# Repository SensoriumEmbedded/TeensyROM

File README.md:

# TeensyROM Multi-capable Cartridge for C64/128

***Connect your Commodore to the 21st century***

**Features include:**
* **TeensyROM+ (PCB v0.4)** is the latest TeensyROM revision — **[see this document](docs/TR+NewFeatures.md)** for additional details:
  * **[TR Host Extensions](docs/TR_Host_Extensions.md)** — Allows others to write and experiment with TR firmware as a .TRH extension, installed alongside the core firmware without modifying it. Envisioned and implemented by [Kelly Fox](https://github.com/kfox) — a huge thank you!
    * [Mean Hamster Power Engine (MPE)](https://meanhamster.com/games/mpe-power-engine) is the first TRH extension, letting your C64 play games never released for it: NES, Game Boy, Doom, classic point-and-click adventures and more. Thank you to [John Swiderski](https://github.com/ziggystar12) for the incredible work and inspiration
  * **Kernal Replacement** — load a custom KERNAL ROM image, with no hardware modification.
  * **512KB REU (RAM Expansion Unit)** — a real REU your C64 software can detect and use
    * Now also works alongside the Retro Replay, Super Snapshot V5, and Final Cartridge III 101% freezers
  * **Freezer Cartridge Support** — Action Replay, Retro Replay, Final Cartridge III and Super Snapshot V5 emulated natively. Thank you to [Paul Harker (LessPaul)](https://github.com/LessPaul) for the freezer contributions!
  * **Remote DMA Memory Access** — give an external app Serial or Ethernet read/write access to C64 memory
    * Supported by [c64cast](https://github.com/kfox/c64cast) — streaming video, audio, visualizations and much more
  * **Battery-Backed Real-Time Clock** — a built-in coin-cell holder: TR+ can remember the correct time through power cycles
  * **External Reset Detect** — press an external reset (C64U button, User port, etc) returns you to the TR menu
  * **Programmable Alternate Button** — the "Alt" button is assignable to whatever's most useful
* All TeensyROM versions:
  * **ROM emulator**: The perfect way to play CRT files, such as the highly recommended [OneLoad64](https://www.youtube.com/watch?v=lz0CJbkplj0) collection.
  * **Instant loader**: [Immediately load/run](docs/General_Usage.md) program (PRG) files
  * **MIDI USB Host & Device, custom ASID Player**: Use a [MIDI keyboard, DAW](docs/MIDI_Usage.md), or [ASID source](docs/ASID_Player.md) to play your SID chip.
  * **Internet interface**: Connect to a [Telnet BBS](docs/Ethernet_Usage.md) or use the integrated [web browser](docs/Browser_Usage.md) to surf/search/download
  * **Remote Control** your C64 using 
    * [NFC Launch System](docs/NFC_Loader.md): The feel of old school cartridges combined with [instant loading](https://www.youtube.com/watch?v=iNfQx2gx0hA)
    * [TeensyROM Suite](https://github.com/MetalHexx/TeensyROM-Suite) (cross-platform): [Trom UI](https://github.com/MetalHexx/TeensyROM-Suite/blob/main/docs/trom-ui.md) with its [DJ Mixer](https://github.com/MetalHexx/TeensyROM-Suite/blob/main/docs/dj-mixer.md), [Trom Terminal](https://github.com/MetalHexx/TeensyROM-Suite/blob/main/docs/trom-terminal.md), the [Trom Agent](https://github.com/MetalHexx/TeensyROM-Suite/blob/main/docs/trom-agent.md) AI companion, and [Trom API](https://github.com/MetalHexx/TeensyROM-Suite/blob/main/docs/trom-api.md) for your own tools
  * SID File Player with voice muting and speed control 
  * Bitmap Picture viewer, Text/PETSCII viewer, Custom BASIC Commands, Autolaunch, *and more* 
  * Lots of games, utilities, pics, and music built-in: no external media required to get started!
  * [**Multiple Hardware Interfaces:**](media/TR_Connections.png) SD card, USB Drive, USB Device and host Ports, Ethernet Port

**C64 Ultimate user?**  See [this list](docs/C64_Ultimate_Enhancements.md) of enhancements the TR brings to your C64U 

*Design by Travis S/Sensorium ([e-mail](mailto:travis@sensoriumembedded.com))* 

||| 
|:--:|:--:|

**Fully assembled/tested TeensyROM+ units** are available via my [Lectronz Shop](https://lectronz.com/products/teensyrom), or via [Tindie](https://www.tindie.com/products/travissmith/teensyrom-cartridge-for-c64128/) or [eBay](https://www.ebay.com/usr/travis_sensorium).

Case/enclosures are available for sale with a new unit (see links above), or [download](3D_Print_Case/3D-Printed-Case-ReadMe.md) and print at home.

Please consider joining us in the [TeensyROM Discord Server](https://discord.gg/ubSAb74S5U) to meet other TeensyROM users, ask questions, provide thoughts/input/feedback, etc.

## Table of contents
  * [TeensyROM Feature Details](#teensyrom-feature-details)
  * [Links to detailed documentation](#links-to-detailed-documentation)
  * [Demo Videos](#demo-videos)
  * [Hardware/PCB Design](#hardware-pcb-design)
  * [Compatibility](#compatibility)
  * [Inspiration and Thank-Yous](#inspiration-and-thank-yous)
  * [Pictures/screen captures](#pictures-screen-captures)

## TeensyROM Feature Details
Compatible with C64 and C128 machines/variants, NTSC and PAL supported.

### **Super fast Loading (.PRG/P00) or ROM emulation (.CRT)** directly from:
  * USB thumb Drive
  * SD card
  * Teensy Internal Flash Memory
  * Transfer directly from your computer using [Trom UI](https://github.com/MetalHexx/TeensyROM-Suite/blob/main/docs/trom-ui.md#copy-files-to-your-cart) (drag and drop, or watch folders), [Trom Terminal](https://github.com/MetalHexx/TeensyROM-Suite/blob/main/docs/trom-terminal.md#copy-files) or [Trom Agent](https://github.com/MetalHexx/TeensyROM-Suite/blob/main/docs/trom-agent.md) from the [TeensyROM Suite](https://github.com/MetalHexx/TeensyROM-Suite)
  * See supported file details [here](https://github.com/SensoriumEmbedded/TeensyROM/blob/main/docs/General_Usage.md#loading-files-and-emulating-roms)
  * [NFC Loading system](docs/NFC_Loader.md) available to quickly select/load with NFC tags.
### **MIDI in/out via USB Host connection:** 
  * Play your SID with a USB MIDI keyboard!
  * Use with popular software such as **Cynthcart, Station64** etc, or the included MIDI2SID app
  * Supports all regular MIDI messages **in and out**
    * Can use your C64 to play a MIDI sound capable device.
  * **Sequential, Datel/Siel, Passport/Sentech, and Namesoft** MIDI cartridges emulated 
  * Use a USB Hub for multiple instruments+thumb drive access
### **MIDI in via USB Device connection:** 
  * Stream .SID or .MIDI files from a modern computer directly to your Commodore machine SID chip!
  * Play MIDI files out of your PC into C64 apps such as Cynthcart or the MIDI2SID app
  * Stream .SID files out of your PC using the ASID MIDI protocol to hear any SID file on original hardware.
### **Internet communication via Ethernet connection**
  * Connect to your favorite C64/128 Telnet BBS!
  * Use with released software such as **CCGMS, StrikeTerm2014, DesTerm128,** etc
  * **Swiftlink** cartridge + 38.4k modem emulation
  * Send AT commands from terminal software to configure the Ethernet connection
  * Sets C64 system time from internet
### **Firmware updates directly from SD card or USB thumb drive**
  * Just drop the .hex file on an SD card or USB drive, no need for extra software to update.

**Key parameters** (startup, Ethernet, timezone, etc.) are stored in internal EEPROM and retained after power down.

## Links to detailed documentation
  * **Usage Documents**
    * **[General Usage](docs/General_Usage.md)**
    * **[MIDI Usage](docs/MIDI_Usage.md)**
    * **[ASID Player](docs/ASID_Player.md)**
    * **[Ethernet Usage](docs/Ethernet_Usage.md)**
    * **[NFC Loading System](docs/NFC_Loader.md)**
    * **[TeensyROM Web Browser](docs/Browser_Usage.md)**
    * **[GEOS 64](docs/GEOS64_Usage.md)**
    * **[GEOS 128](docs/GEOS128_Usage.md)**
    * **[Custom BASIC Commands](docs/Custom_BASIC_Commands.md)**
    * **[TR Host Extensions (TR+ only)](docs/TR_Host_Extensions.md)**
    * **[USB/Ethernet Remote Command Protocol](docs/ControlComms.md)**
  * **SW Release notes/development**
    * **[Firmware Release history](bin/TeensyROM/FW_Release_History.md)**
    * **[Software Build Instructions](Source/BuildInfo.md)**
  * **Hardware & PCB Related**
    * **[3D printed case files/document](3D_Print_Case/3D-Printed-Case-ReadMe.md)**
    * **[RTC Battery Addition for v0.2/0.3 PCBs](docs/RTC_Battery_Addition.md)**
    * **[TeensyROM Assembly Instructions](PCB/PCB_Assembly.md)**
    * **[PCB Design History](PCB/PCB_History.md)**
    * **[Bill of materials with cost info](https://github.com/SensoriumEmbedded/TeensyROM/raw/main/PCB/v0.3/TeensyROM%20v0.3%20BOM.xlsx)**
    * **[PDF Schematic](https://github.com/SensoriumEmbedded/TeensyROM/raw/main/PCB/v0.3/TeensyROM_v0.3_Schem.pdf)**

## Demo Videos:
  * **[This YouTube Playlist](https://www.youtube.com/playlist?list=PL3fTdu8e_1iChAsRr9KjWtC3A8Ql8IaDn)** contains all the latest TeensyROM demo videos, such as: 
    * Real-time video/audio capture of menu navigation and loading/running/emulating various programs/cartridges
    * Demo using Cynthcart and Datel MIDI emulation to play with a USB keyboard 
    * MIDI ASID Demo: Stream .SID & .MIDI files directly to your C64/SID
    * Web Browser and internet file download demo 
    * SID Player and Picture viewer demo 
  * **[SID DJ on Commodore 64 (ft. TeensyROM)](https://youtu.be/PjhqYkmsScg)**: SID tunes mixed live on real C64s in the Trom UI [DJ Mixer](https://github.com/MetalHexx/TeensyROM-Suite/blob/main/docs/dj-mixer.md), plus a [Scratch / Beat Juggle](https://youtu.be/xoJBOEPB5IY) preview

## Compatibility
* TeensyROM compatability has been fully validated on **many** different NTSC **and** PAL machines: C64, C64C, SX-64, and C128 as well as modern reproductions such as the C64U, Ultimate 64, EVO64, Mega65 (r5 and higher), and Reloaded MKII
* The early "prototype" version of breadbin (PCA 326298 w/ 5 pin video) has a known issue with the reset circuit that must be corrected to be compatible with the TeensyROM and other fastload cartridges. See [this post](https://www.lemon64.com/forum/viewtopic.php?t=74222) or [this video](https://youtu.be/agDFLPP9yIw?t=813) for instructions on how to correct this issue.
* Some NTSC C128s show an intermittent DMA write issue (used by REU, Remote DMA, etc.) — see **[TR+ NTSC C128 DMA Findings](docs/TR+NTSC_C128_DMA_Findings.md)** for symptoms, cause, and the fix.

## Hardware/PCB Design
PCB 0.2/0.3 Component selection was done using parts large enough (SOIC and 0805s at the smallest) that any soldering enthusiast should be able to assemble themselves.   Since high volume production wasn't necessarily the vision for this device, 2 sided SMT was used to reduce the PCB size while still accommodating larger IC packages.

*The original TR (v0.2/0.3) — publicly self-buildable today; see [assembly instructions](PCB/PCB_Assembly.md).*

Beginning with PCB v0.4 (TeensyROM+) the package sizes are reduced (TSSOP and 0603 passives) to allow additional needed circuitry and single sided manufacturing.

**A note about overclocking**
The Teensy 4.1 is slightly "overclocked" to 816MHz from FW in this design. Per the app, external cooling is not required for this speed.  However, in abundance of caution, a heatsink is specified in the BOM for this project.  In addition, the temperature can be read on the setup screen of the main TeensyROM app. The max spec is 95C, and there is a panic shutdown at 90C.  In my experience, even on a warm day running for hours with no heatsink, the temp doesn't exceed 75C.

## Inspiration and Thank-Yous:
* [**Heather S**](https://www.instagram.com/dalliancecreations/): Loving wife, continuous encourager, saintly patience
* [**MetalHexx**](https://github.com/MetalHexx): Big picture ideas, remote control via the [TeensyROM Suite](https://github.com/MetalHexx/TeensyROM-Suite), testing, friendship
* [**Kelly Fox**](https://github.com/kfox): TR+ contributions ([Host Extensions](docs/TR_Host_Extensions.md), build system and much more), [c64cast](https://github.com/kfox/c64cast)
* [**John Swiderski**](https://github.com/ziggystar12) of Mean Hamster Software: [MPE](https://meanhamster.com/games/mpe-power-engine), the first TR Host Extension, and the inspiration behind them
* [**Paul Harker aka LessPaul**](https://github.com/LessPaul): Freezer cartridge contributions (Action Replay, Retro Replay, Final Cartridge III, Super Snapshot V5)
* [**Avrilcadabra**](https://www.youtube.com/@avrilcadabra): Musician, experimenter, provider of ideas and feedback 
* [**Paul D aka Digitalman**](https://www.youtube.com/@digitalman4404): Thought provoker, promoter, Maker, and tester extraordinaire
* [**Stefan Wessels**](https://github.com/StewBC): Cartridge case design
* [**StatMat**](https://github.com/Stat-Mat): NFC Scanner idea, Fast boot code, OneLoad64 creation
* **Giants with tall shoulders**: SID/SIDEKick, KungFu Flash, VICE Team

## Pictures/screen captures:
|||
|:--:|:--:|

|||
|:--:|:--:|
|||
|||

See the [media](media/) folder for more pics and screen shots.

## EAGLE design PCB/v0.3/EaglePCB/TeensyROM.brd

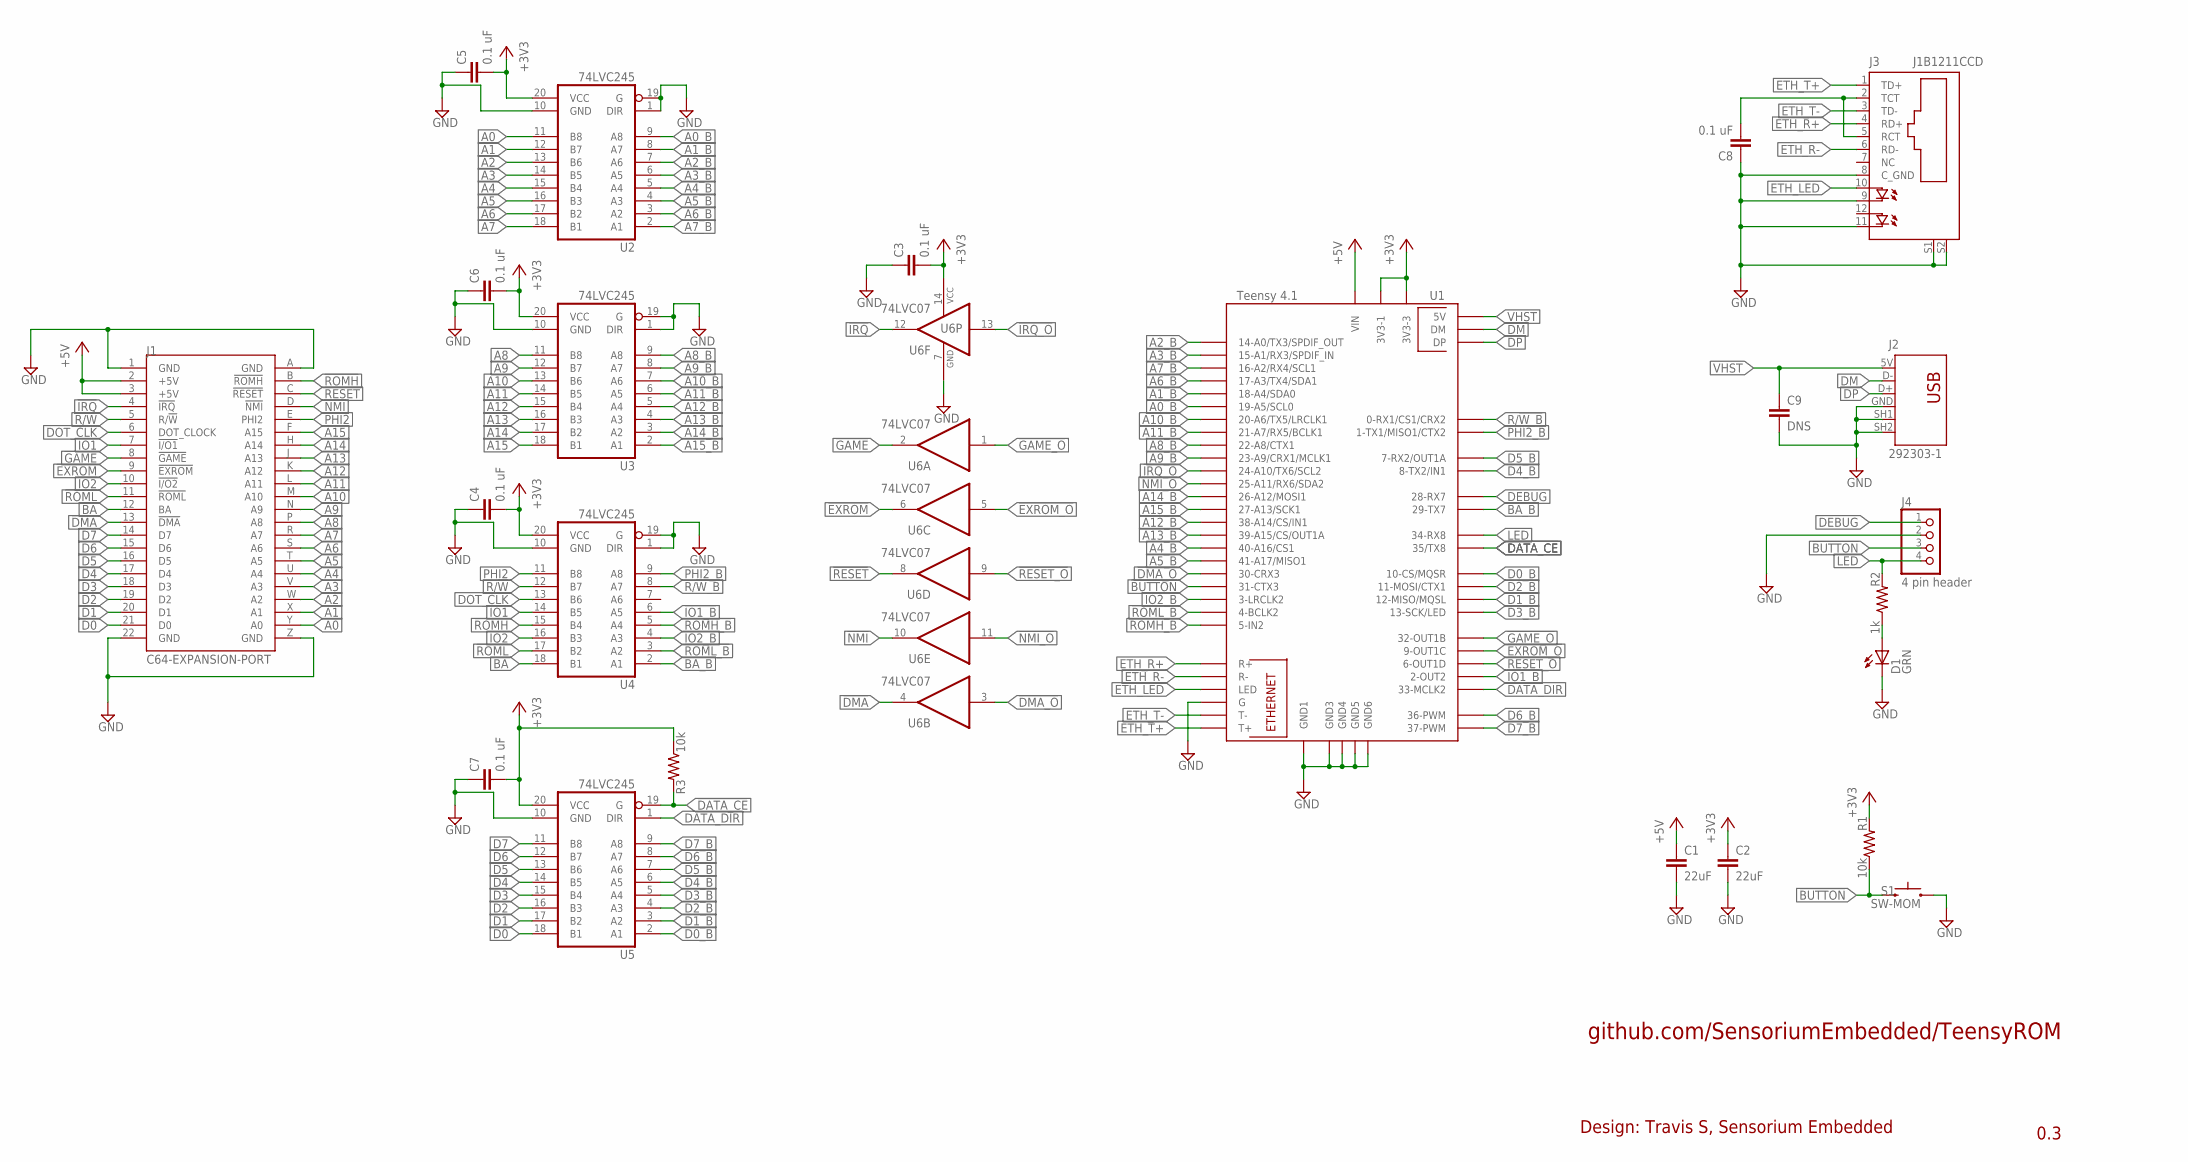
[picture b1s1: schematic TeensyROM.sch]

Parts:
C1, C2: 22uF; C1210
C3, C4, C5, C6, C7, C8: 0.1 uF; 0805
C9: DNS; C1210
D1: GRN; LED-3MM-PTH
J1: C64-EXPANSION-PORT; EXPANSIO_SQ
J2: 292303-1; USB
J3: J1B1211CCD; CONN12_J1B1211CCD_WIZ
J4: 4 pin header; 1X04
R1, R3: 10k; R0805
R2: 1k; R0805
S1: SW-MOM; TACTILE-PTH
U1: Teensy 4.1; TEENSY41
U2, U3, U4, U5: 74LVC245; SO20W
U6: 74LVC07; SO14

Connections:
!BUTTON: J4.3, R1.1, S1.3 (2), U1.31-CTX3
!DATA_CE: R3.2, U1.35-TX8 (35/TX8), U5.19 (G)
!DMA: J1.13 (!DMA), U6.4 (O)
!DMA_O: U1.30-CRX3, U6.3 (I)
!EXROM: J1.9 (!EXROM), U6.6 (O)
!EXROM_O: U1.9-OUT1C, U6.5 (I)
!GAME: J1.8 (!GAME), U6.2 (O)
!GAME_O: U1.32-OUT1B, U6.1 (I)
!IO1: J1.7 (!I/O1), U4.14 (B5)
!IO1_B: U1.2-OUT2, U4.6 (A5)
!IO2: J1.10 (!I/O2), U4.16 (B3)
!IO2_B: U1.3-LRCLK2, U4.4 (A3)
!IRQ: J1.4 (!IRQ), U6.12 (O)
!IRQ_O: U1.24-A10/TX6/SCL2, U6.13 (I)
!NMI: J1.D (!NMI), U6.10 (O)
!NMI_O: U1.25-A11/RX6/SDA2, U6.11 (I)
!RESET: J1.C (!RESET), U6.8 (O)
!RESET_O: U1.6-OUT1D, U6.9 (I)
!ROMH: J1.B (!ROMH), U4.15 (B4)
!ROMH_B: U1.5-IN2, U4.5 (A4)
!ROML: J1.11 (!ROML), U4.17 (B2)
!ROML_B: U1.4-BCLK2, U4.3 (A2)
+3V3: C2.1, C3.2, C4.2, C5.2, C6.2, C7.2, R1.2, R3.1, U1.3V3-1, U1.3V3-3, U2.20 (VCC), U3.20 (VCC), U4.20 (VCC), U5.20 (VCC), U6.14 (VCC)
+5V: C1.1, J1.2 (+5V), J1.3 (+5V), U1.VIN
A0: J1.Y (A0), U2.11 (B8)
A0_B: U1.19-A5/SCL0, U2.9 (A8)
A1: J1.X (A1), U2.12 (B7)
A1_B: U1.18-A4/SDA0, U2.8 (A7)
A2: J1.W (A2), U2.13 (B6)
A2_B: U1.14-A0/TX3/SPDIF_OUT, U2.7 (A6)
A3: J1.V (A3), U2.14 (B5)
A3_B: U1.15-A1/RX3/SPDIF_IN, U2.6 (A5)
A4: J1.U (A4), U2.15 (B4)
A4_B: U1.40-A16/CS1, U2.5 (A4)
A5: J1.T (A5), U2.16 (B3)
A5_B: U1.41-A17/MISO1, U2.4 (A3)
A6: J1.S (A6), U2.17 (B2)
A6_B: U1.17-A3/TX4/SDA1, U2.3 (A2)
A7: J1.R (A7), U2.18 (B1)
A7_B: U1.16-A2/RX4/SCL1, U2.2 (A1)
A8: J1.P (A8), U3.11 (B8)
A8_B: U1.22-A8/CTX1, U3.9 (A8)
A9: J1.N (A9), U3.12 (B7)
A9_B: U1.23-A9/CRX1/MCLK1, U3.8 (A7)
A10: J1.M (A10), U3.13 (B6)
A10_B: U1.20-A6/TX5/LRCLK1, U3.7 (A6)
A11: J1.L (A11), U3.14 (B5)
A11_B: U1.21-A7/RX5/BCLK1, U3.6 (A5)
A12: J1.K (A12), U3.15 (B4)
A12_B: U1.38-A14/CS/IN1, U3.5 (A4)
A13: J1.J (A13), U3.16 (B3)
A13_B: U1.39-A15/CS/OUT1A, U3.4 (A3)
A14: J1.H (A14), U3.17 (B2)
A14_B: U1.26-A12/MOSI1, U3.3 (A2)
A15: J1.F (A15), U3.18 (B1)
A15_B: U1.27-A13/SCK1, U3.2 (A1)
BA: J1.12 (BA), U4.18 (B1)
BA_B: U1.29-TX7, U4.2 (A1)
D0: J1.21 (D0), U5.18 (B1)
D0_B: U1.10-CS\MQSR (10-CS/MQSR), U5.2 (A1)
D1: J1.20 (D1), U5.17 (B2)
D1_B: U1.12-MISO/MQSL, U5.3 (A2)
D2: J1.19 (D2), U5.16 (B3)
D2_B: U1.11-MOSI/CTX1, U5.4 (A3)
D3: J1.18 (D3), U5.15 (B4)
D3_B: U1.13-SCK/LED, U5.5 (A4)
D4: J1.17 (D4), U5.14 (B5)
D4_B: U1.8-TX2/IN1, U5.6 (A5)
D5: J1.16 (D5), U5.13 (B6)
D5_B: U1.7-RX2/OUT1A, U5.7 (A6)
D6: J1.15 (D6), U5.12 (B7)
D6_B: U1.36-PWM, U5.8 (A7)
D7: J1.14 (D7), U5.11 (B8)
D7_B: U1.37-PWM, U5.9 (A8)
DATA_DIR: U1.33-MCLK2, U5.1 (DIR)
DEBUG: J4.1, U1.28-RX7
DM: J2.D- (2), U1.DM
DOT_CLK: J1.6 (DOT_CLOCK), U4.13 (B6)
DP: J2.D+ (3), U1.DP
ETH_CT: C8.2, J3.2 (TCT), J3.5 (RCT)
ETH_LED: J3.10 (A), U1.LED
ETH_R+: J3.4 (RD+), U1.R+
ETH_R-: J3.6 (RD-), U1.R-
ETH_T+: J3.1 (TD+), U1.T+
ETH_T-: J3.3 (TD-), U1.T-
GND: C1.2, C2.2, C3.1, C4.1, C5.1, C6.1, C7.1, C8.1, C9.2, D1.K (C), J1.1 (GND), J1.22 (GND), J1.A (GND), J1.Z (GND), J2.GND (4), J2.SH1 (5), J2.SH2 (6), J3.8 (C_GND), J3.9 (C), J3.11 (C1), J3.S1, J3.S2, J4.2, S1.1, U1.G, U1.GND1, U1.GND3, U1.GND4, U1.GND5, U1.GND6, U2.1 (DIR), U2.10 (GND), U2.19 (G), U3.1 (DIR), U3.10 (GND), U3.19 (G), U4.1 (DIR), U4.10 (GND), U4.19 (G), U5.10 (GND), U6.7 (GND)
LED: J4.4, R2.2, U1.34-RX8
LED_R: D1.A, R2.1
PHI2: J1.E (PHI2), U4.11 (B8)
PHI2_B: U1.1-TX1/MISO1/CTX2, U4.9 (A8)
R/!W: J1.5 (R/!W), U4.12 (B7)
R/!W_B: U1.0-RX1/CS1/CRX2, U4.8 (A7)
VHST: C9.1, J2.5V (1), U1.+5V (5V)

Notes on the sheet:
0.3
github.com/SensoriumEmbedded/TeensyROM
Design: Travis S, Sensorium Embedded

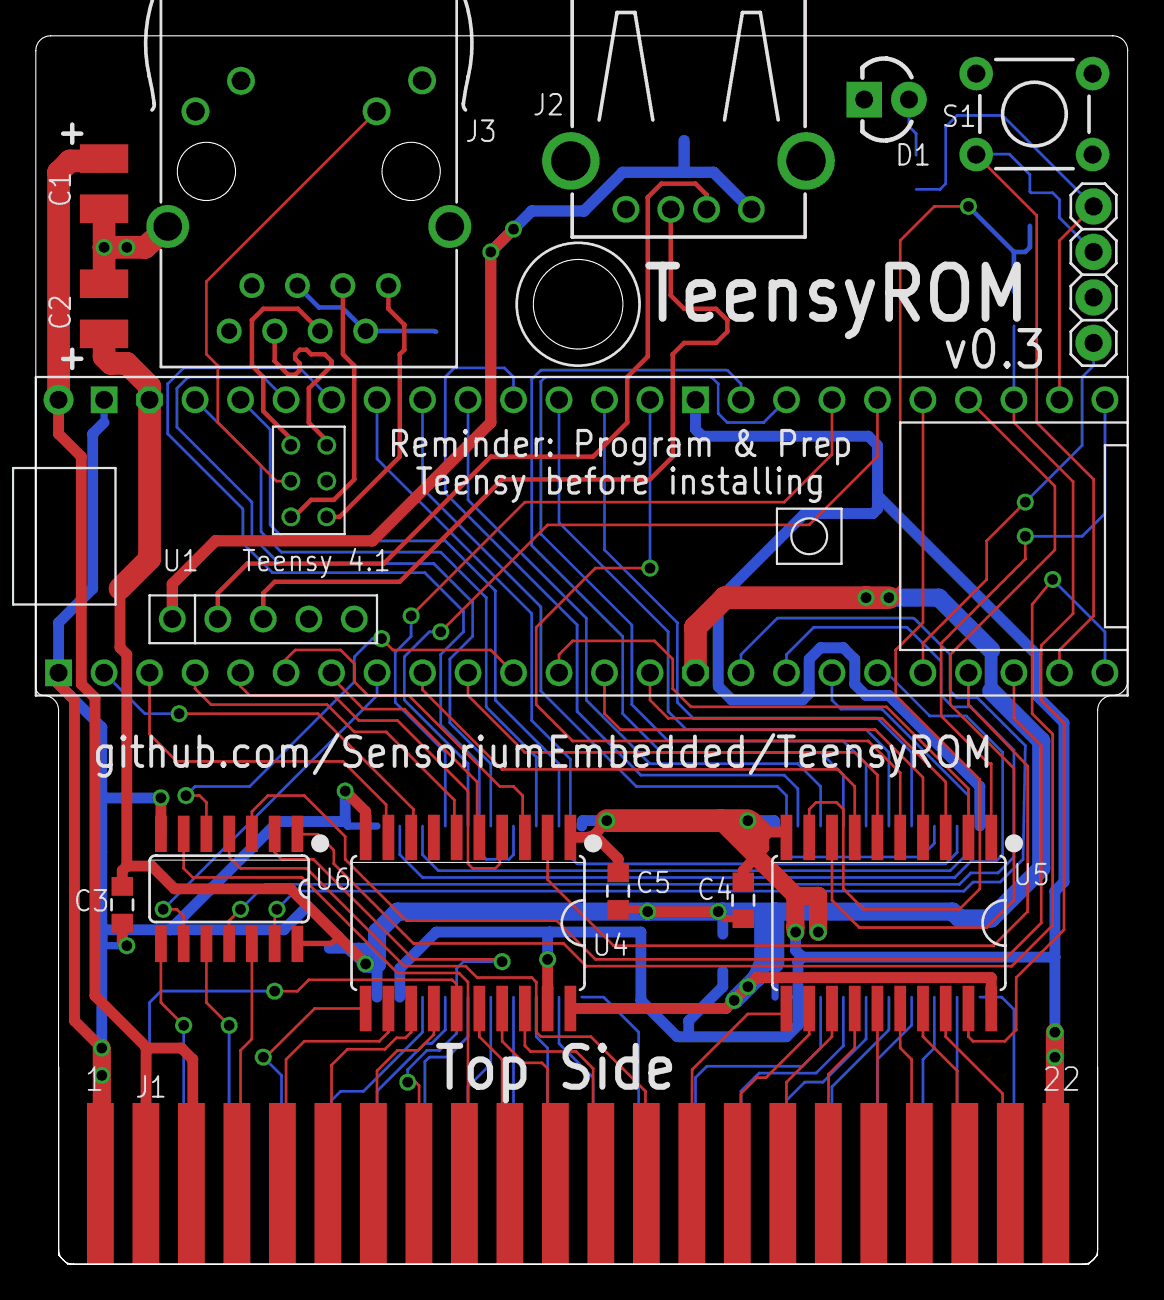
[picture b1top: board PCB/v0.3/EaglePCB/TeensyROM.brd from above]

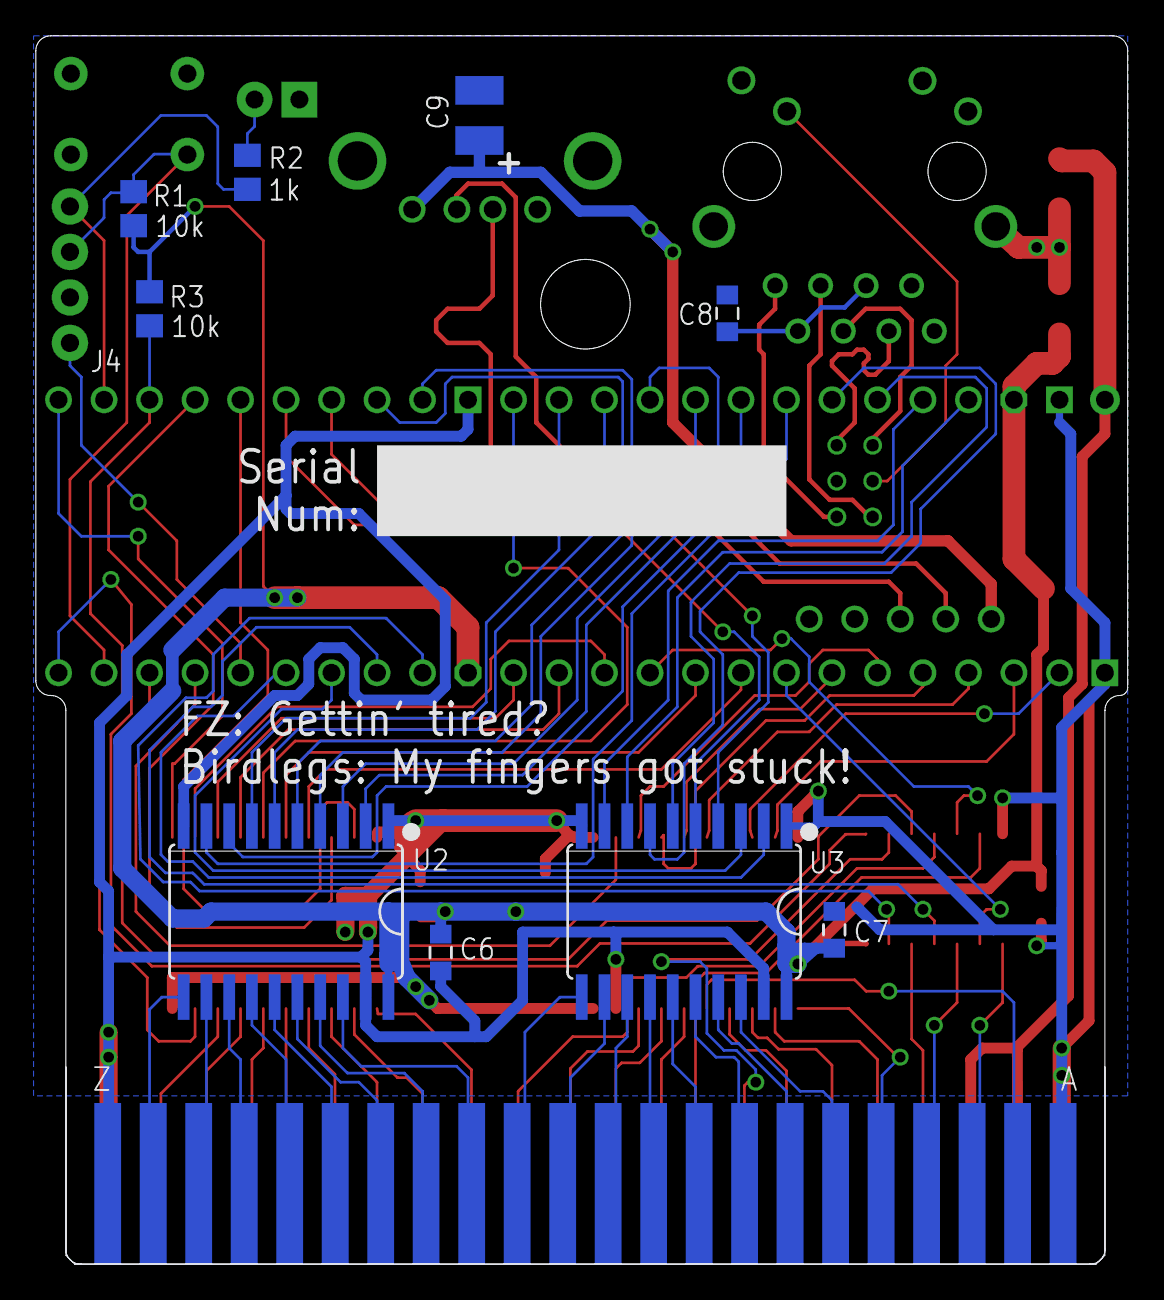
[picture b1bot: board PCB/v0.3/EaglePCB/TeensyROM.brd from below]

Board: 2 copper layers, 61.0 x 68.6 mm, 25 parts (9 on the bottom side), 93 nets.

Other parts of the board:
U$1: 3,0

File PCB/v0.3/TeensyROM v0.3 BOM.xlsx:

BOM item # | Qty | Locations/RefDes | Value | Manuf | MPN Highlighted=No Sub | DigiKey PN/link | Cost ea (USD) July 2023 | Extended Cost (USD) | Notes
1 | 1 | PCB | 2 layer 0.063" PCB | OSH Park, JLCPCB, PCBWay | TeensyROM v0.2c | n/a | 10.799999999999999 | 10.799999999999999 | 2 layer board: 2.40 x 2.70 x 0.063 inches Recommend ENIG finish, 30° chamfered 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
2 | 1 | R2 | RES 0805 1K | TE Connectivity | CRG0805F1K0 | A106056CT-ND | 0.1 | 0.1
3 | 2 | R1,R3 | RES 0805 10K | TE Connectivity | CRG0805F10K | A106054CT-ND | 0.1 | 0.2
4 | 6 | C3, C4, C5, C6, C7,C8 | CAP 0805 CER 0.1UF 50V X7R | Samsung | CL21B104KBCNNNC | 1276-1003-1-ND | 0.1 | 0.60000000000000009
5 | 4 | U2, U3, U4, U5 | 74LVC245, SO20W/N | Nexperia Texas Instruments Texas Instruments | 74LVC245AD,118 (Wide) SN74LVC245ADW (Wide) SN74LVC245ANSR (Nar) | 1727-3104-1-ND 296-1232-5-ND 296-13632-1-ND | 0.68 | 2.72 | Octal Bus Transceiver, 3-state Recommend wide package, but any of these 3 will 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
6 | 1 | U6 | 74LVC07, SO14 | Texas Instruments OnSemi | SN74LVC07ADR MC74LCX07 | 296-8441-1-ND MC74LCX07DR2GOSCT-ND | 0.5 | 0.5 | Hex BUFFER, open collector HV output Either of these two will work
7 | 1 | U1 | Teensy 4.1 Devel Board w/ Ethernet | PJRC | TEENSY41 | 1568-DEV-16771-ND | 33.08 | 33.08 | Be sure to pre-program and then cut the 5v power jumper on the back (see assy i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
8 | 2 | U1-Hdr 1/2 | CONN HEADER VERT 1x24 POS 2.54mm (0.1") | Würth | 61302411121 | 732-5331-ND | 1.31 | 2.62 | For Teensy main connections to TeensyROM
9 | 1 | U1-Hdr 3 | CONN HEADER VERT 1x5 POS 2.54mm (0.1") | Würth | 61300511121 | 732-5318-ND | 0.26 | 0.26 | For Teensy USB Host connection to TeensyROM.
10 | 1 | U1-Hdr 4 | CONN HEADER VERT 6POS (2x3) 2MM | METZ CONNECT | PR20C03VBDN | 1849-1000-ND | 0.19 | 0.19 | For Teensy Ethernet connection to TeensyROM.
11 | 1 | S1 | SW-MOM-TACTILE | C&K | PTS645SL50-2 LFS | CKN9092-ND | 0.19 | 0.19
12 | 1 | D1 | LED-3MM-GRN | Lumex Opto | SSL-LX3044GD | 67-1060-ND | 0.43 | 0.43 | Polarity: Sq hole = short lead = flat side = '-'(Neg) = Cathode
13 | 2 | C1, C2 | CAP CER 22UF 16V X5R 1210 | Samsung | CL32A226MOJNNNE | 1276-1851-1-ND | 0.37 | 0.74
14 | 1 | J3 | RJ-45 w/ Transformer | Cetus/WIZNet | J1B1211CCD | 1278-1052-ND | 3.78 | 3.78 | CONN JACK 1PORT 100 BASE-T PCB
15 | 1 | J2 | USB-A Female | TE/AMP | 292303-1 | A31726-ND | 1.61 | 1.61 | CONN RCPT USB2.0 TYPEA 4POS R/A
16 | 1 | U1 Heatsink | 12x12mm Aluminum heatsink w/ thermal tape attached Max height to fit in case: ~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 | Jeteokar | B0B7K2TWZM | https://www.amazon.com/dp/B0B7K2TWZM or https://www.ebay.com/itm/115401351474 | 0.499 | 0.499 | Optional, but recommended Can sub other 12x12mm heatsinks/pads
16a | 1 | U1 Therm Pad | 11x11mm Thermal Conductive Adhesive Tape | Multiple subs, such as these w/ thermal tape attached | t-Global TG-T1000-11-11-0.25-5PT | 1168-TG-T1000-11-11-0.25-5PT-ND | 0.2 | 0.2 | If needed (recommended heatsink has thermal pad included)
17 | 1 | C9 | 1210 cap | Do not stuff |  |  |  |  | Not required
18 | 1 | J4 | CONN HEADER VERT 1x4 POS 0.1" | Do not stuff |  |  |  |  | Not required
19 | 1 | J1 | C64-EXPANSION-PORT Gold Fingers | Do not stuff |  |  |  |  | Part of PCB
20 | 2 | U1-Rcpt 1/2 | CONN RCPT VERT 1x24 POS 0.1" |  |  |  |  |  | if socketting Teensy
21 | 1 | U1-Rcpt 3 | CONN RCPT VERT 1x5 POS 0.1" |  |  |  |  |  | if socketting Teensy USB
22 | 1 | U1-Rcpt 4 | CONN RCPT 6POS 0.079 PCB | METZ CONNECT | FR20C03VBDN | 1849-1152-ND |  |  | if socketting Teensy Eth
23 | 1 | U1-EthDongl | Ethernet Kit for Teensy 4.1 | PJRC | ETHERNET_KIT |  |  |  | if not using on-board conns
24 | 1 | U1-USBDongl | USB Host Cable For Teensy 4.1 | PJRC | CABLE_USB_HOST_T36 |  |  |  | if not using on-board conns
 |  |  |  |  |  |  | Raw Total: | 58.518999999999998
 |  |  |  |  |  |  | 10% S&H | 5.8519000000000005
 |  |  |  |  |  |  | Parts total | 64.370900000000006
 |  |  |  |  |  |  | Hand Assy+test | 15 | 1 hour labor
 |  |  |  |  |  | Total: Assembled and tested |  | 79.370900000000006
 |  |  |  |  |  |  | Plus shipping | tbd

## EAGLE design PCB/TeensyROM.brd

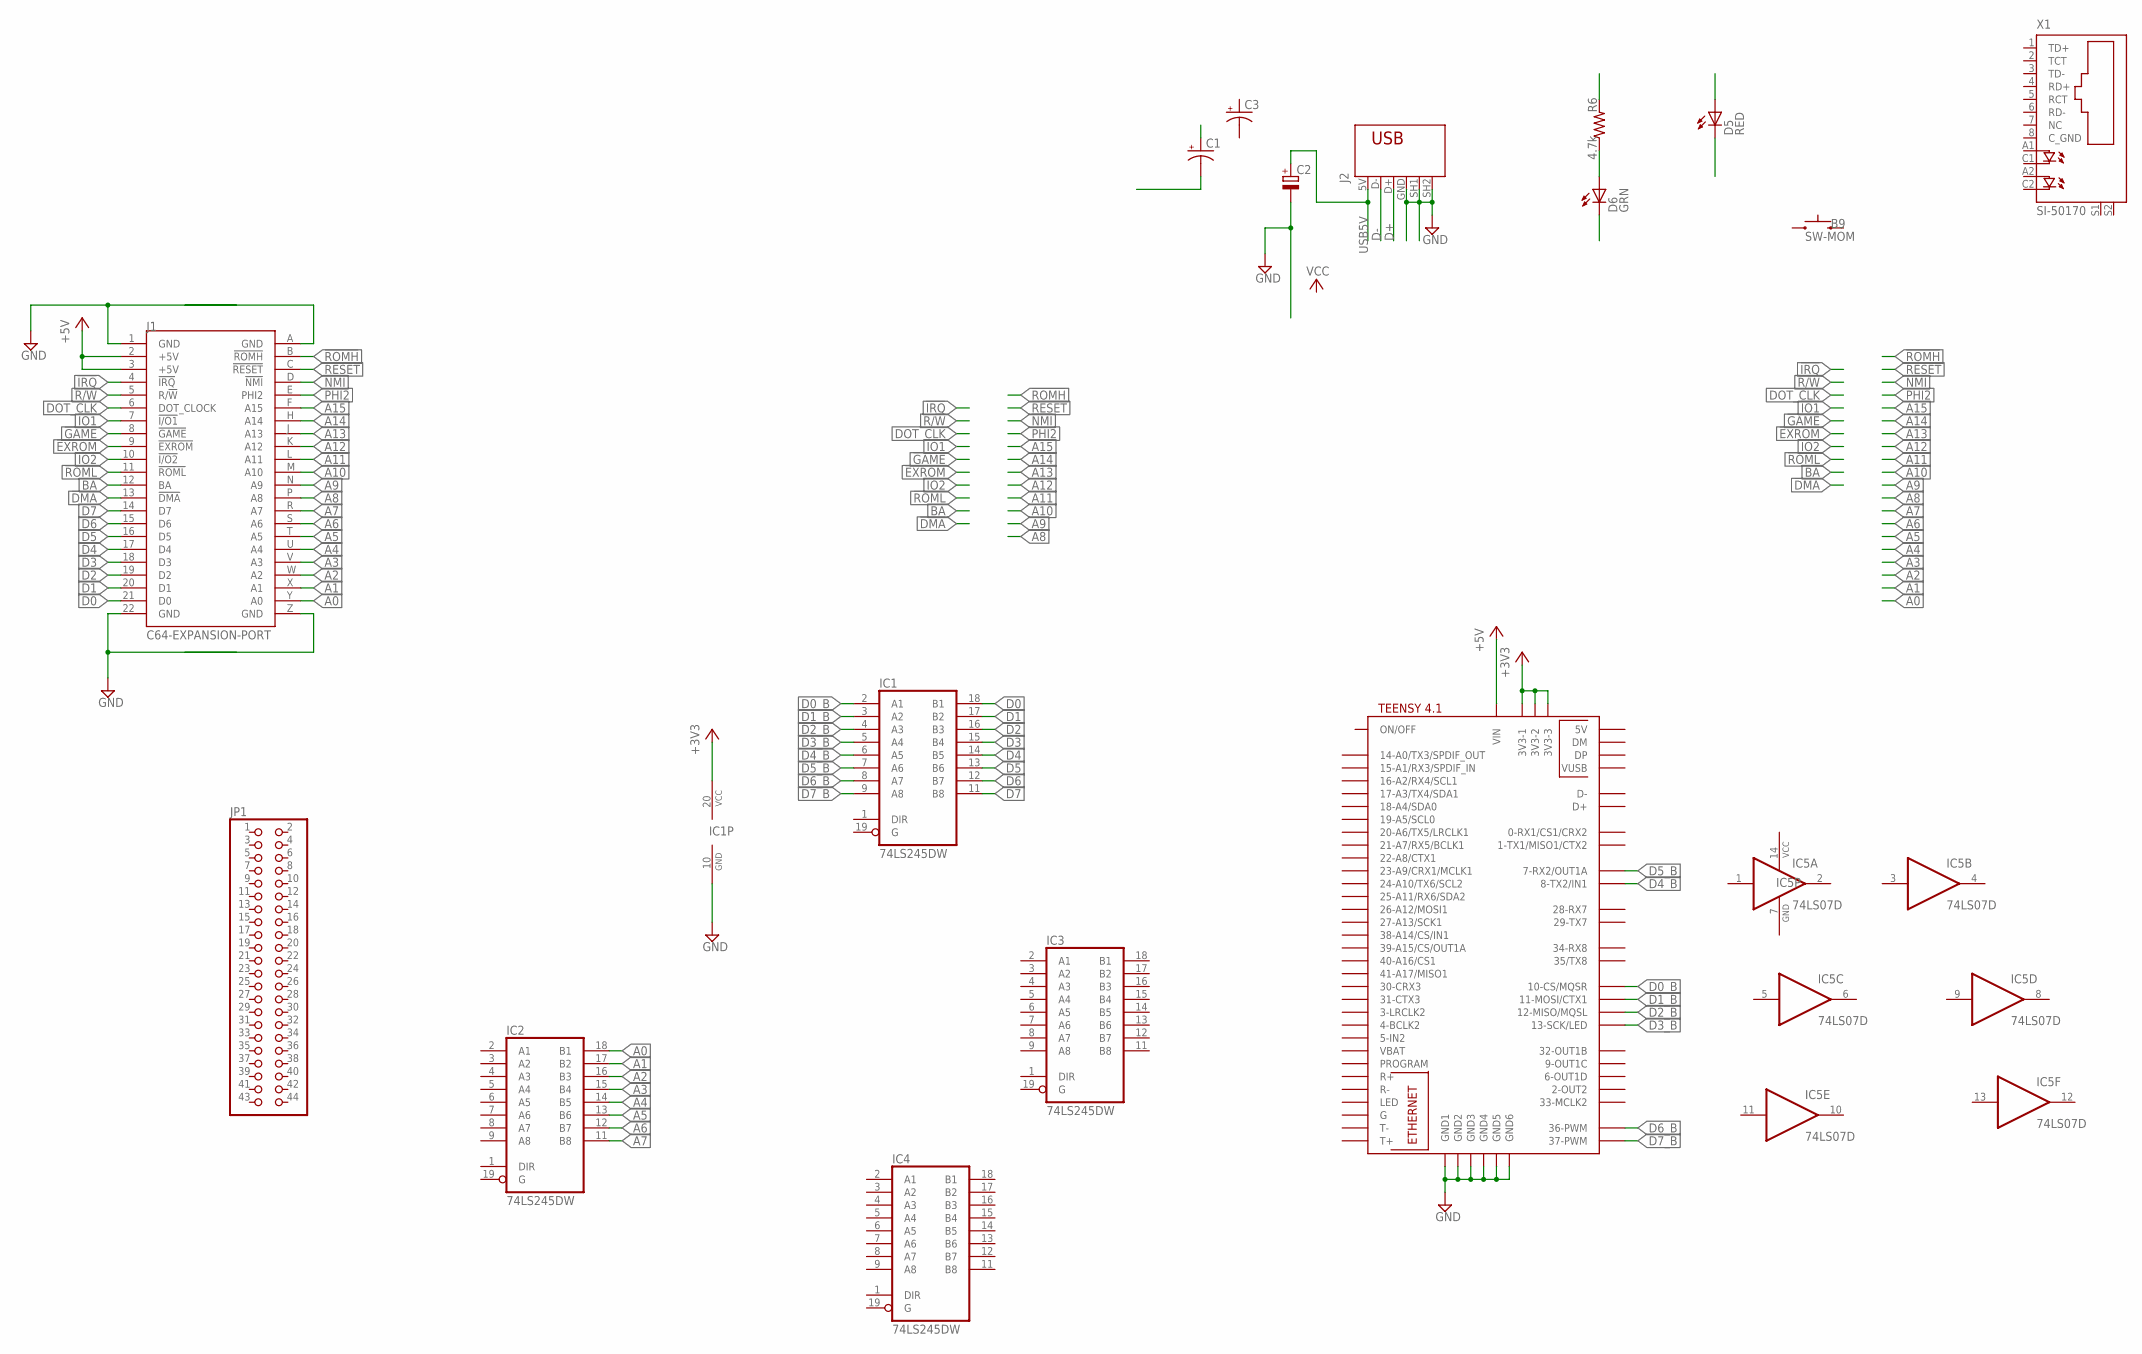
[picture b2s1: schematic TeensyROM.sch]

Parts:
B9: SW-MOM; TACTILE-PTH
C1, C3: CPOL-USE2.5-6; E2,5-6
C2: CPOL-EUA/3216-18W; A/3216-18W
D5: RED; LED-3MM-PTH
D6: GRN; LED-3MM-PTH
IC1, IC2, IC3, IC4: 74LS245DW; SO20W
IC5: 74LS07D; SO14
J1: C64-EXPANSION-PORT; EXPANSIO_SQ
J2: USB-787616; USB
JP1: PINHD-2X22; 2X22
R6: 4.7k; R0805
U$1: TEENSY41
X1: SI-50170

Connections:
!DMA: J1.13 (!DMA)
!EXROM: J1.9 (!EXROM)
!GAME: J1.8 (!GAME)
!IO1: J1.7 (!I/O1)
!IO2: J1.10 (!I/O2)
!IRQ: J1.4 (!IRQ)
!NMI: J1.D (!NMI)
!RESET: J1.C (!RESET)
!ROMH: J1.B (!ROMH)
!ROML: J1.11 (!ROML)
+3V3: IC1.20 (VCC), U$1.3V3-1, U$1.3V3-2, U$1.3V3-3
+5V: J1.2 (+5V), J1.3 (+5V)
+5V1: C1.+
A0: IC2.18 (B1), J1.Y (A0)
A1: IC2.17 (B2), J1.X (A1)
A2: IC2.16 (B3), J1.W (A2)
A3: IC2.15 (B4), J1.V (A3)
A4: IC2.14 (B5), J1.U (A4)
A5: IC2.13 (B6), J1.T (A5)
A6: IC2.12 (B7), J1.S (A6)
A7: IC2.11 (B8), J1.R (A7)
A8: J1.P (A8)
A9: J1.N (A9)
A10: J1.M (A10)
A11: J1.L (A11)
A12: J1.K (A12)
A13: J1.J (A13)
A14: J1.H (A14)
A15: J1.F (A15)
B12: D5.K (C)
BA: J1.12 (BA)
D0: IC1.18 (B1), J1.21 (D0)
D0_B: IC1.2 (A1), U$1.10-CS\MQSR (10-CS/MQSR)
D1: IC1.17 (B2), J1.20 (D1)
D1_B: IC1.3 (A2), U$1.11-MOSI/CTX1
D2: IC1.16 (B3), J1.19 (D2)
D2_B: IC1.4 (A3), U$1.12-MISO/MQSL
D3: IC1.15 (B4), J1.18 (D3)
D3_B: IC1.5 (A4), U$1.13-SCK/LED
D4: IC1.14 (B5), J1.17 (D4)
D4_B: IC1.6 (A5), U$1.8-TX2/IN1
D5: IC1.13 (B6), J1.16 (D5)
D5_B: IC1.7 (A6), U$1.7-RX2/OUT1A
D6: IC1.12 (B7), J1.15 (D6)
D6_B: IC1.8 (A7), U$1.36-PWM
D7: IC1.11 (B8), J1.14 (D7)
D7_B: IC1.9 (A8), U$1.37-PWM
D+: J2.D+ (3)
D-: J2.D- (2)
DOT_CLK: J1.6 (DOT_CLOCK)
GND: C2.-, IC1.10 (GND), IC2.10 (GND), IC3.10 (GND), IC4.10 (GND), IC5.7 (GND), J1.1 (GND), J1.22 (GND), J2.GND (4), J2.SH1 (5), J2.SH2 (6), U$1.GND1, U$1.GND2, U$1.GND3, U$1.GND4, U$1.GND5, U$1.GND6
GND1: J1.A (GND), J1.Z (GND)
GND2: D6.K (C)
GND3: C1.-
unnamed: D6.A, R6.1
PHI2: J1.E (PHI2)
R/!W: J1.5 (R/!W)
USB5V: C2.+, J2.5V (1)
VCC: IC2.20 (VCC), IC3.20 (VCC), IC4.20 (VCC), IC5.14 (VCC)
VCC1: R6.2

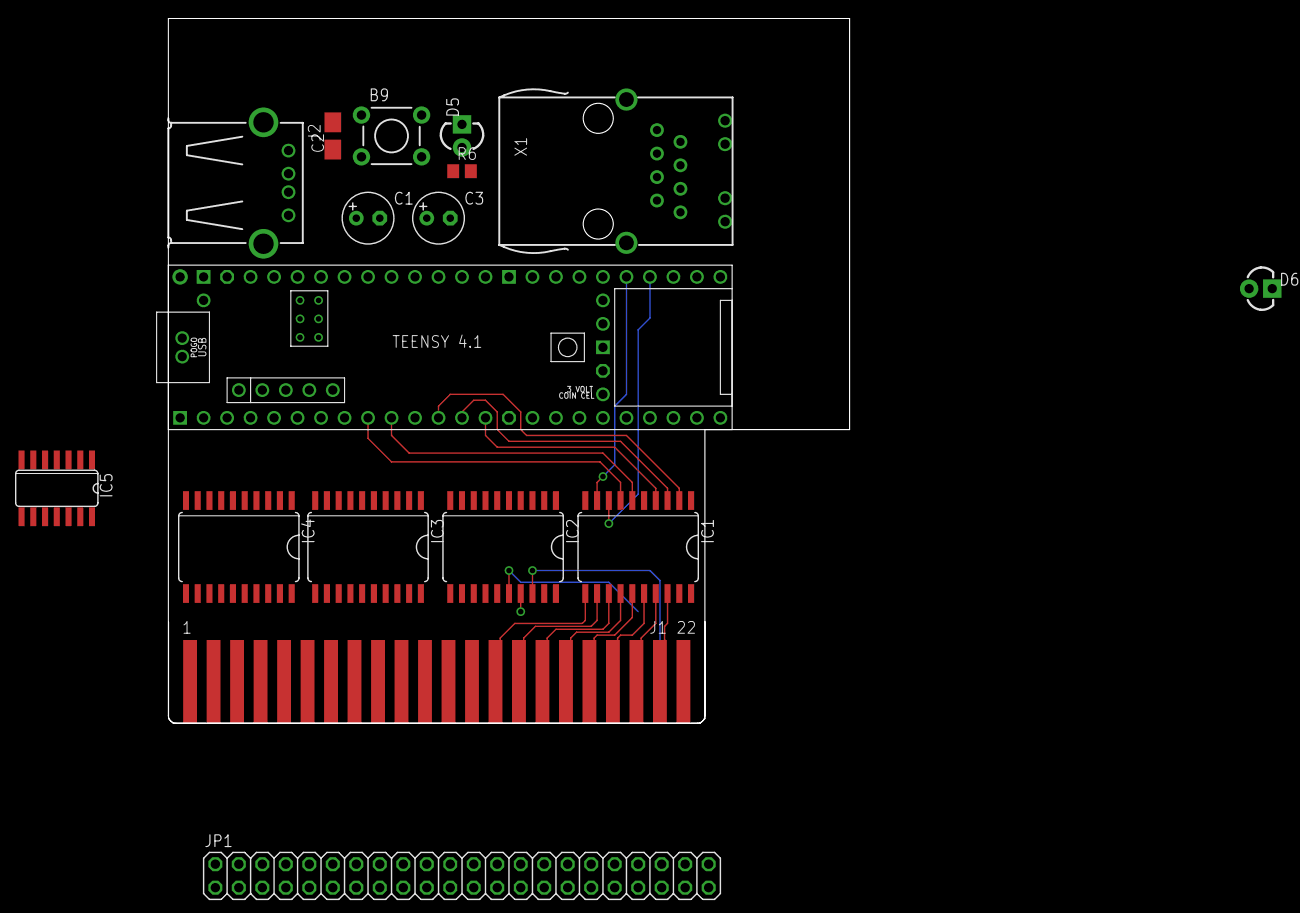
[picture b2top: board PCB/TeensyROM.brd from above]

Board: 2 copper layers, 73.7 x 76.2 mm, 17 parts (0 on the bottom side), 31 nets.

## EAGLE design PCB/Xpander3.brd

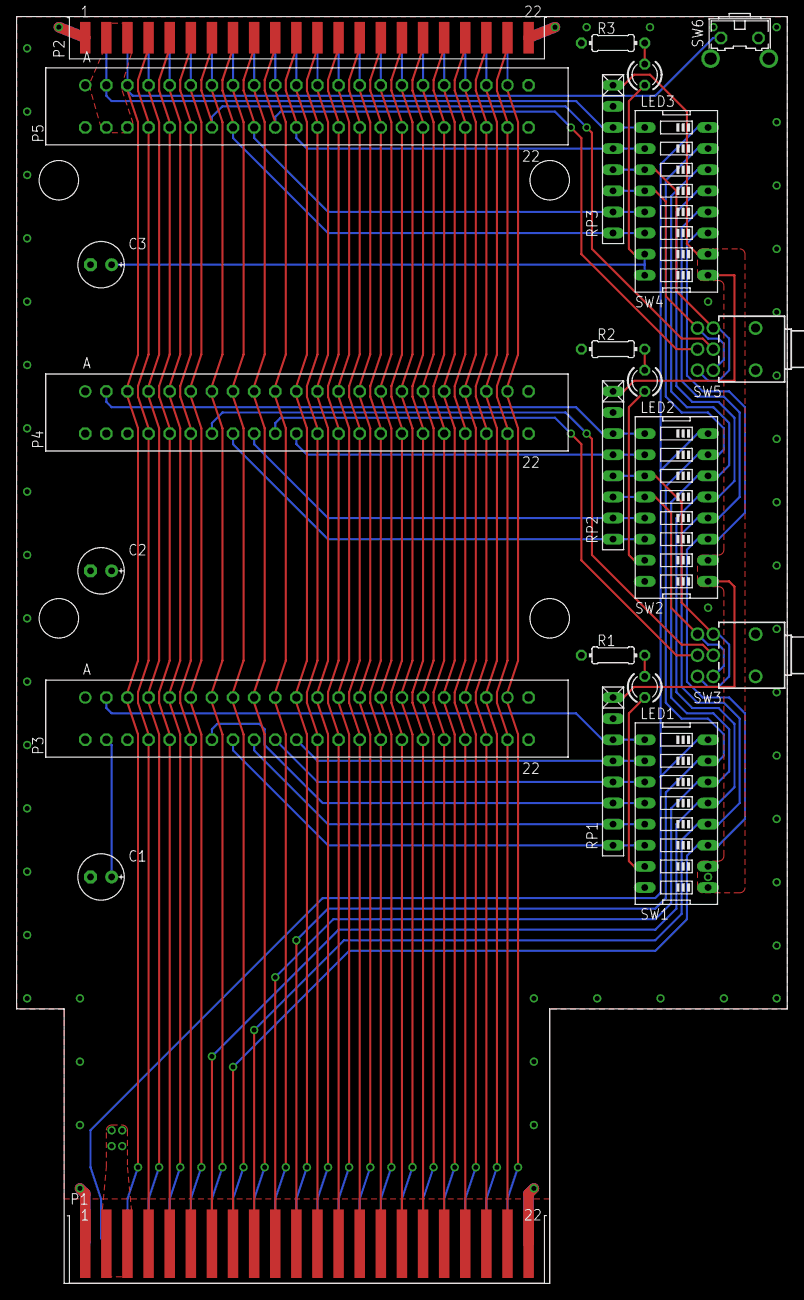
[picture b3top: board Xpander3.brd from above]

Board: 2 copper layers, 92.7 x 152.4 mm, 24 parts (1 on the bottom side), 69 nets.

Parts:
C1, C2, C3: 47uF; E2,5-6E
F1: 1812L
LED1, LED2, LED3: LED3MM
P1: MA22-2; 44PINEDGE
P2: MA22-2SH; MA22-2_SHORT
P3, P4, P5: FE22-2
R1, R2, R3: 330; 0204/7
RP1, RP2, RP3: 10K; RN-8
SW1, SW2, SW4: EDG-08
SW3, SW5: TL46WO; TL4XWO
SW6: !RESET; B3F-31XX

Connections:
4: P1.4, P2.4, P3.4, P4.4, P5.4
5: P1.5, P2.5, P3.5, P4.5, P5.5
6: P1.6, P2.6, P3.6, P4.6, P5.6
7: P1.7, SW1.5, SW2.5, SW4.5
8: P1.8, SW1.3, SW2.3, SW4.3
9: P1.9, SW1.4, SW2.4, SW4.4
10: P1.10, SW1.6, SW2.6, SW4.6
11: P1.11, SW1.7, SW2.7, SW4.7
12: P1.12, P2.12, P3.12, P4.12, P5.12
13: P1.13, P2.13, P3.13, P4.13, P5.13
14: P1.14, P2.14, P3.14, P4.14, P5.14
15: P1.15, P2.15, P3.15, P4.15, P5.15
16: P1.16, P2.16, P3.16, P4.16, P5.16
17: P1.17, P2.17, P3.17, P4.17, P5.17
18: P1.18, P2.18, P3.18, P4.18, P5.18
19: P1.19, P2.19, P3.19, P4.19, P5.19
20: P1.20, P2.20, P3.20, P4.20, P5.20
21: P1.21, P2.21, P3.21, P4.21, P5.21
B: P1.B, SW1.8, SW2.8, SW4.8
C: P1.C, P2.C, P3.C, P4.C, P5.C, SW6.2
D: P1.D, P2.D, P3.D, P4.D, P5.D
E: P1.E, P2.E, P3.E, P4.E, P5.E
F: P1.F, P2.F, P3.F, P4.F, P5.F
FVCC: F1.P$1, RP1.1, RP2.1, RP3.1, SW1.1, SW1.2, SW2.1, SW2.2, SW4.1, SW4.2
GND: C1.-, C2.-, C3.-, P1.1, P1.22, P1.A, P1.Z, P2.1, P2.22, P2.A, P2.Z, P3.1, P3.22, P3.A, P3.Z, P4.1, P4.22, P4.A, P4.Z, P5.1, P5.22, P5.A, P5.Z, R1.1, R2.1, R3.1, SW6.1
H: P1.H, P2.H, P3.H, P4.H, P5.H
J: P1.J, P2.J, P3.J, P4.J, P5.J
K: P1.K, P2.K, P3.K, P4.K, P5.K
L: P1.L, P2.L, P3.L, P4.L, P5.L
M: P1.M, P2.M, P3.M, P4.M, P5.M
N: P1.N, P2.N, P3.N, P4.N, P5.N
unnamed: P3.7, RP1.6, SW1.12
unnamed: P3.8, RP1.8, SW1.14
unnamed: P3.9, RP1.7, SW1.13
unnamed: P3.10, RP1.5, SW1.11
unnamed: P3.11, RP1.4, SW1.10
unnamed: P3.B, RP1.3, SW1.9
unnamed: C1.+, LED1.A, P3.2, P3.3, SW1.15, SW1.16
unnamed: C2.+, LED2.A, P4.2, P4.3, SW2.15, SW2.16
unnamed: RP2.6, SW2.12, SW3.3, SW3.4
unnamed: P4.11, RP2.4, SW2.10
unnamed: P4.9, RP2.7, SW2.13
unnamed: P4.8, RP2.8, SW2.14
unnamed: P4.B, RP2.3, SW2.9
unnamed: RP2.5, SW2.11, SW3.1, SW3.6
unnamed: LED1.K, R1.2
unnamed: P2.9, P5.9, RP3.7, SW4.13
unnamed: P4.10, SW3.5
unnamed: P2.11, P5.11, RP3.4, SW4.10
unnamed: P2.B, P5.B, RP3.3, SW4.9
unnamed: C3.+, LED3.A, P2.2, P2.3, P5.2, P5.3, SW4.15, SW4.16
unnamed: P4.7, SW3.2
unnamed: P2.8, P5.8, RP3.8, SW4.14
unnamed: LED2.K, R2.2
unnamed: LED3.K, R3.2
unnamed: P2.7, P5.7, SW5.2
unnamed: P2.10, P5.10, SW5.5
unnamed: RP3.6, SW4.12, SW5.3, SW5.4
unnamed: RP3.5, SW4.11, SW5.1, SW5.6
P: P1.P, P2.P, P3.P, P4.P, P5.P
R: P1.R, P2.R, P3.R, P4.R, P5.R
S: P1.S, P2.S, P3.S, P4.S, P5.S
T: P1.T, P2.T, P3.T, P4.T, P5.T
U: P1.U, P2.U, P3.U, P4.U, P5.U
V: P1.V, P2.V, P3.V, P4.V, P5.V
VCC: F1.P$2, P1.2, P1.3
W: P1.W, P2.W, P3.W, P4.W, P5.W
X: P1.X, P2.X, P3.X, P4.X, P5.X
Y: P1.Y, P2.Y, P3.Y, P4.Y, P5.Y

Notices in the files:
parts and their libraries:
TeensyROM: COPYRIGHT: Copyright (C) 2023 Ultra Librarian. All rights reserved.
